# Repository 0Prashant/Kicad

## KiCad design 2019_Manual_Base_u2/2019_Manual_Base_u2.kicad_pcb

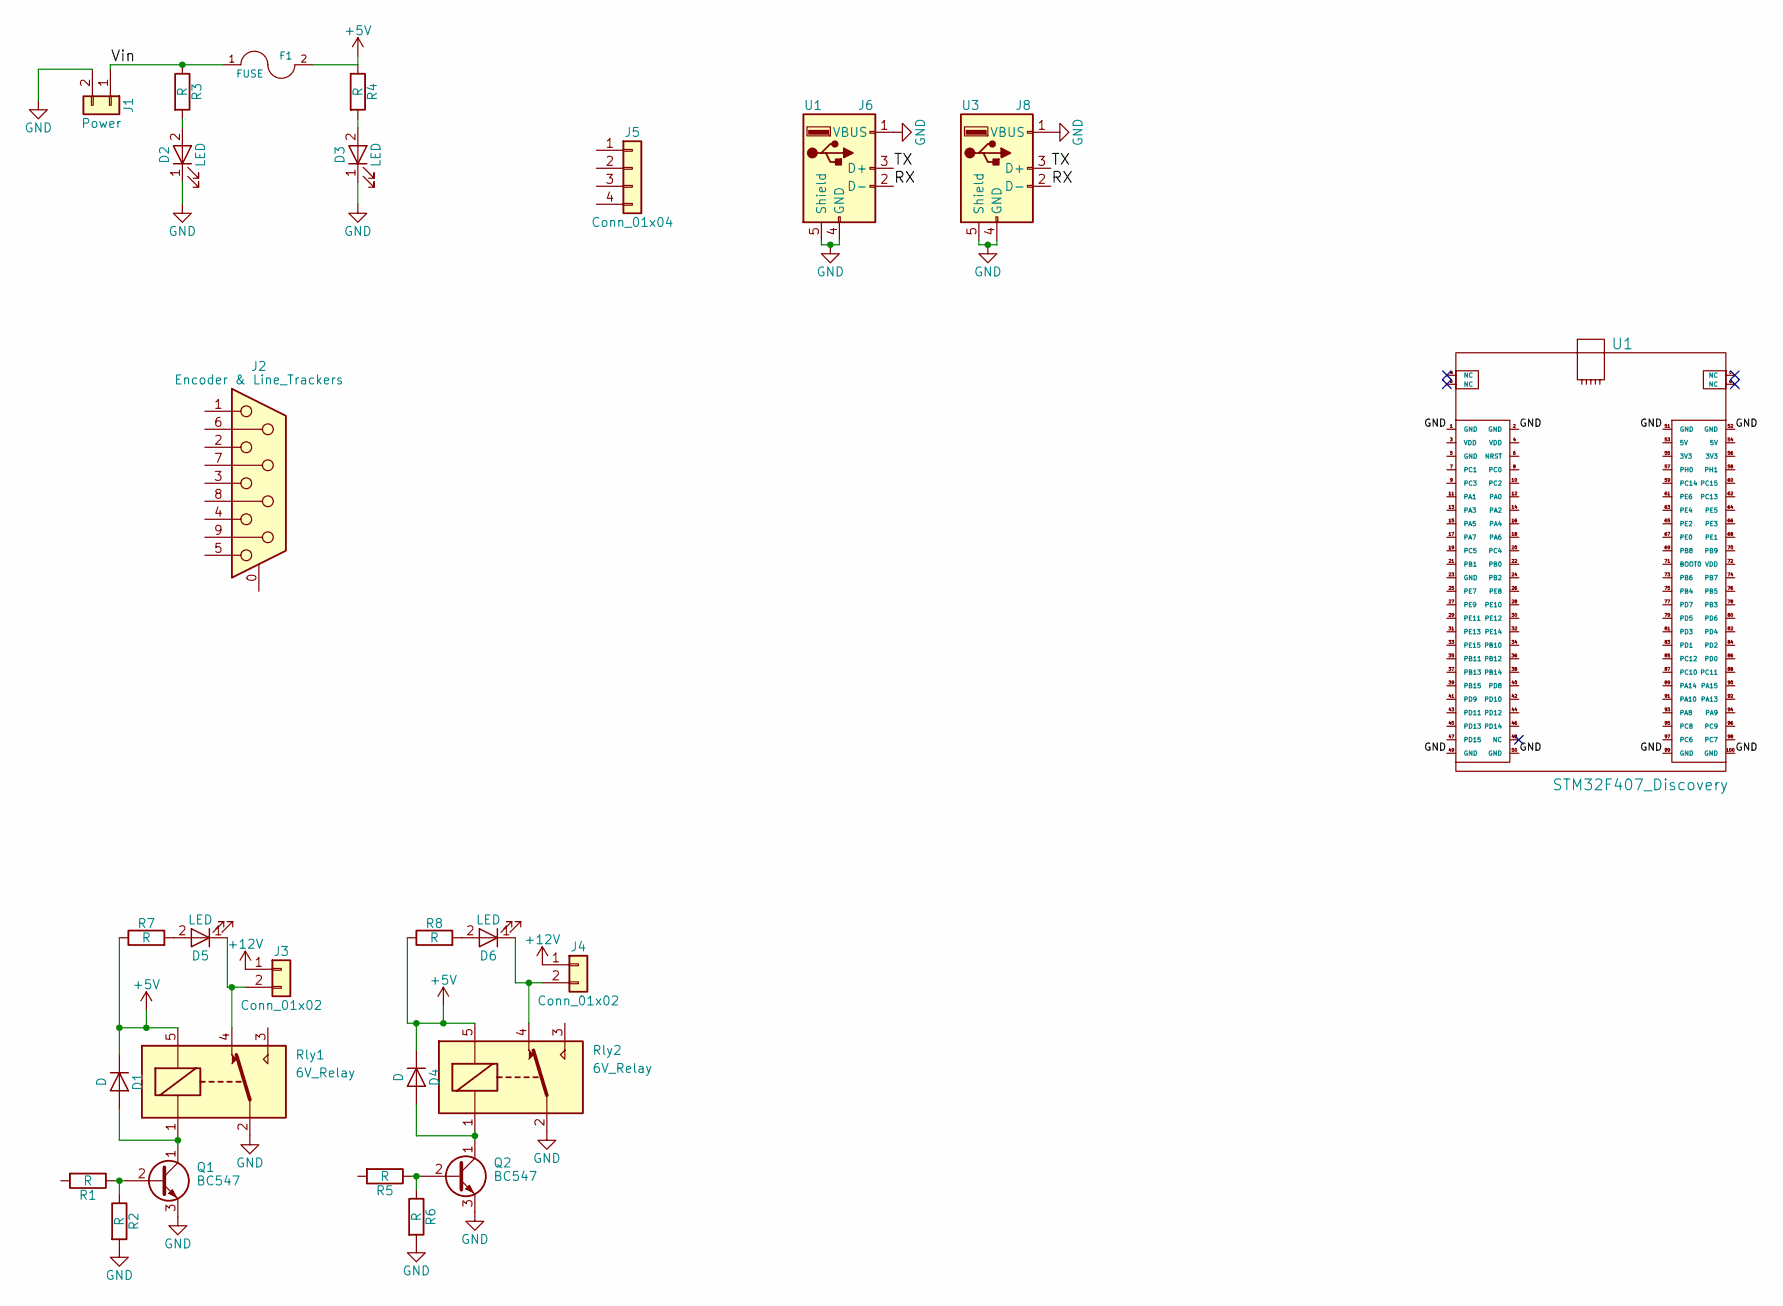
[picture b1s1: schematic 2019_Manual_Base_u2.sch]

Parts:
D1, D4: D; Diode_Small
D2, D3, D5, D6: LED; LED_D3.0mm
F1: FUSE; Fuse_Holder
J1: Power; Solar_Connector
J2: Encoder & Line_Trackers; Connector_DB_9
J3, J4: Conn_01x02; Connector_Bornier_2
J5: Conn_01x04; Pin_Header_Straight_1x04_Pitch2.54mm
J6: U1; Connector_USB
J8: U3; Connector_USB
Q1, Q2: BC547
R1, R2, R3, R4, R5, R6, R7, R8: R; Resistor_small
Rly1, Rly2: 6V_Relay; Relay_6V
U1: STM32F407_Discovery

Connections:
+5V: D1.1 (K), D4.1 (K), F1.2, R4.1, R7.1, R8.1, Rly1.5, Rly2.5
+12V: J3.1, J4.1
/RX: J6.2 (D-), J8.2 (D-)
/TX: J6.3 (D+), J8.3 (D+)
/Vin: F1.1, J1.1, R3.1
GND: D2.1 (K), D3.1 (K), J1.2, J6.1 (VBUS), J6.4 (GND), J6.5 (Shield), J8.1 (VBUS), J8.4 (GND), J8.5 (Shield), Q1.3 (E), Q2.3 (E), R2.2, R6.2, Rly1.2, Rly2.2, U1.1 (GND), U1.2 (GND), U1.49 (GND), U1.50 (GND), U1.51 (GND), U1.52 (GND), U1.99 (GND), U1.100 (GND)
unnamed: D1.2 (A), Q1.1 (C), Rly1.1
unnamed: D2.2 (A), R3.2
unnamed: D3.2 (A), R4.2
unnamed: D4.2 (A), Q2.1 (C), Rly2.1
unnamed: D5.1 (K), J3.2, Rly1.4
unnamed: D5.2 (A), R7.2
unnamed: D6.1 (K), J4.2, Rly2.4
unnamed: D6.2 (A), R8.2
unnamed: Q1.2 (B), R1.1, R2.1
unnamed: Q2.2 (B), R5.1, R6.1

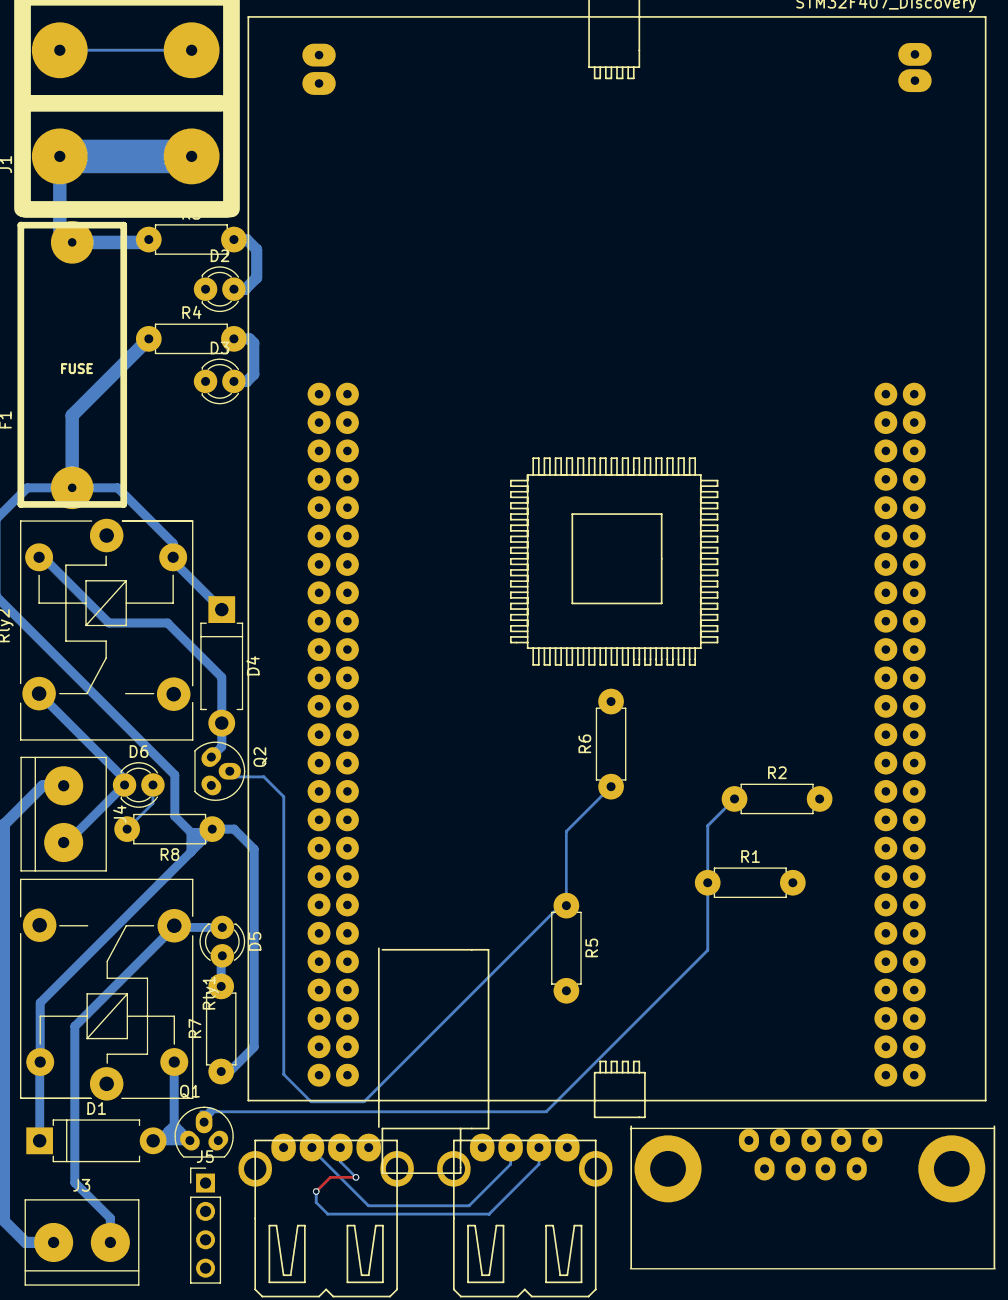
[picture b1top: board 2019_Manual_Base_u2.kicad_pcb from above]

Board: 2 copper layers, 27 parts (0 on the bottom side), 16 nets.

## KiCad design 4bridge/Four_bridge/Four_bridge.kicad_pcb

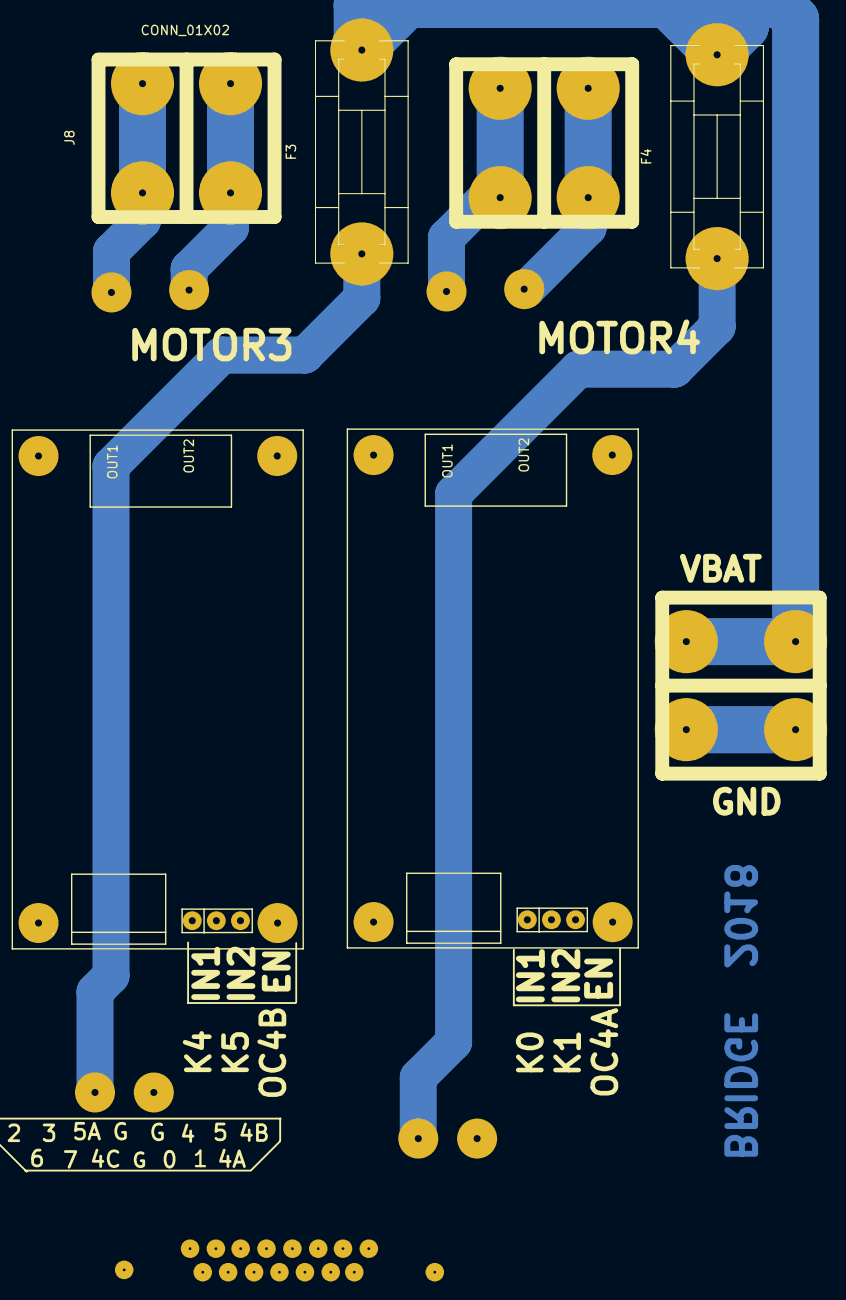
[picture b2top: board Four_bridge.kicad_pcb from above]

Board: 2 copper layers, 8 parts (0 on the bottom side), 14 nets.

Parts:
F3, F4: Fuse; Fuseholder5x20_horiz_SemiClosed_Casing10x25mm
J2: DB15_MALE; DB15MC
J4, J8, J11: CONN_01X02; Solar_connector
J7: H-Bridge3; H_Bridge
J10: H-Bridge4; H_Bridge

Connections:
/GND: J2.4, J2.5, J2.12, J4.2, J7.7, J10.7
/M31: J2.7, J7.4
/M32: J2.6, J7.5
/M41: J2.14, J10.4
/M42: J2.15, J10.5
/OUT31: J7.1, J8.1
/OUT32: J7.2, J8.2
/OUT41: J10.1, J11.1
/OUT42: J10.2, J11.2
/PWM3: J2.8, J7.3
/PWM4: J2.13, J10.3
/VBAT: F3.2, F4.2, J4.1
/VBAT3: F3.1, J7.6
/VBAT4: F4.1, J10.6

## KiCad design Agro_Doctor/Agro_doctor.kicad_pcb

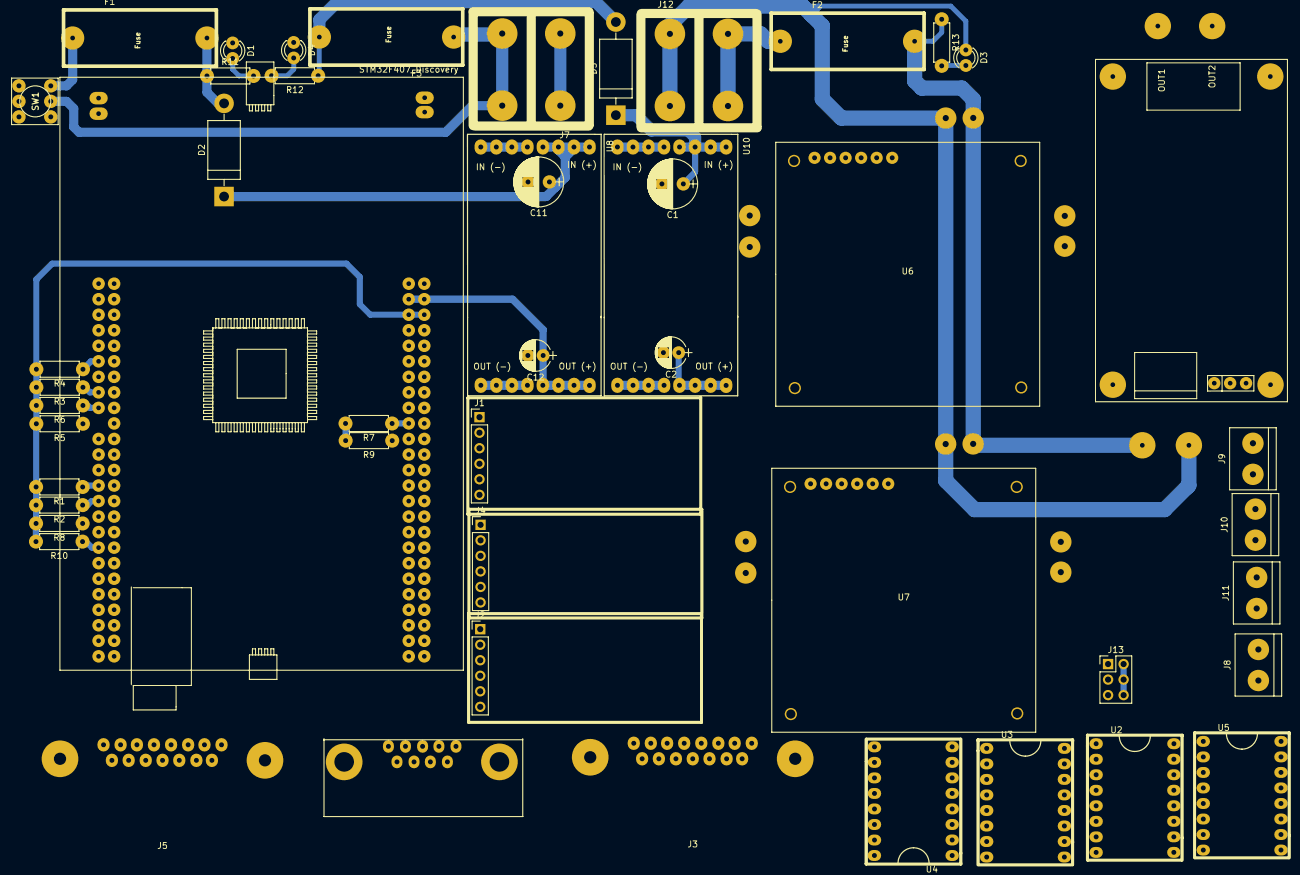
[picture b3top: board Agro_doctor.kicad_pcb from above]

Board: 2 copper layers, 49 parts (0 on the bottom side), 33 nets.

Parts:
C1, C11: 100uf; Capacitor_100uF
C2, C12: 10uf; Capacitor_10uF
D1, D3, D4: LED; LED_D3.0mm
D2, D5: D; Diode_Medium
F1, F2, F3: Fuse; Fuse_Holder
J1, J2, J4: Bluetooth; Pin_Header_Straight_1x06_Pitch2.54mm
J3: 3STEPPER,1SERVO; Connector_DB15
J5: Encoders, Stepper1; Connector_DB15
J6: 3 MPU, HUMIDITY, PH; Connector_DB_9
J7: Power_Logic; Solar_Connector
J8: M1; Connector_Bornier_2
J9: M4; Connector_Bornier_2
J10: M2; Connector_Bornier_2
J11: M3; Connector_Bornier_2
J12: Power_Motor; Solar_Connector
J13: MS_Conn; Pin_Header_Straight_2x03_Pitch2.54mm
R1, R2, R3, R4, R5, R6, R7, R8, R9, R10: 10K; Resistor_small
R11, R13: 1k5; Resistor_small
R12: R; Resistor_small
SW1: SW_DIP_x01; DIP_Switch
U1: Motor_Driver; H_Bridge
U2: A4988_1; A4998
U3: A4988_2; A4998
U4: A4988_3; A4998
U5: A4988_4; A4998
U6: L298_M2,3; L298
U7: L298_M4; L298
U8: Buck; Buck_Regulator
U9: STM32F407_Discovery
U10: Boost; Buck_Regulator

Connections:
+3V3: J6.5, R1.2, R2.2, R3.2, R4.2, R5.2, R6.2, R7.2, R8.2, R9.2, R10.2, U9.55, U9.56
+5V: C12.1, J1.5, J2.5, J3.8, J4.5, J5.14, J6.9, J13.4, J13.5, J13.6, U8.3, U9.53, U9.54
+12V: F3.2, J7.2, SW1.1
/12VMOT: F2.1, R13.1, U1.6, U6.1, U7.1
/18V: C2.1, U10.3
/E1_CHA: J5.13, R1.1, U9.27
/E1_CHB: J5.12, R2.1, U9.29
/E2_CHA: J5.11, R3.1, U9.15
/E2_CHB: J5.5, R4.1, U9.11
/E3_CHA: J5.4, R5.1, U9.18
/E3_CHB: J5.3, R6.1, U9.17
/GMOT: D3.1, J12.1, U1.7, U6.2, U7.2
/I2C1_SCL: J6.7, R7.1, U9.69
/I2C1_SDA: J6.6, R9.1, U9.70
/I2C2_SCL: J6.4, R8.1, U9.34
/I2C2_SDA: J6.1, R10.1, U9.35
/SERVO: J3.15, U9.91
/U1_RX: J1.3, U9.74
/U1_TX: J1.2, U9.73
/U2_RX: J2.3, U9.13
/U2_TX: J2.2, U9.14
/U3_RX: J4.3, U9.88
/U3_TX: J4.2, U9.87
GND: C1.2, C2.2, C11.2, C12.2, D1.1, D4.1, J1.4, J2.4, J3.7, J4.4, J5.7, J6.8, J7.1, U8.2, U8.4, U9.1, U9.2, U9.49, U9.50, U9.51, U9.52, U9.99, U9.100, U10.2, U10.4
unnamed: C1.1, D5.1, U10.1
unnamed: C11.1, D2.1, U8.1
unnamed: D1.2, R11.2
unnamed: D2.2, F1.1, R11.1
unnamed: D3.2, R13.2
unnamed: D4.2, R12.2
unnamed: D5.2, F3.1, R12.1
unnamed: F1.2, SW1.2
unnamed: F2.2, J12.2

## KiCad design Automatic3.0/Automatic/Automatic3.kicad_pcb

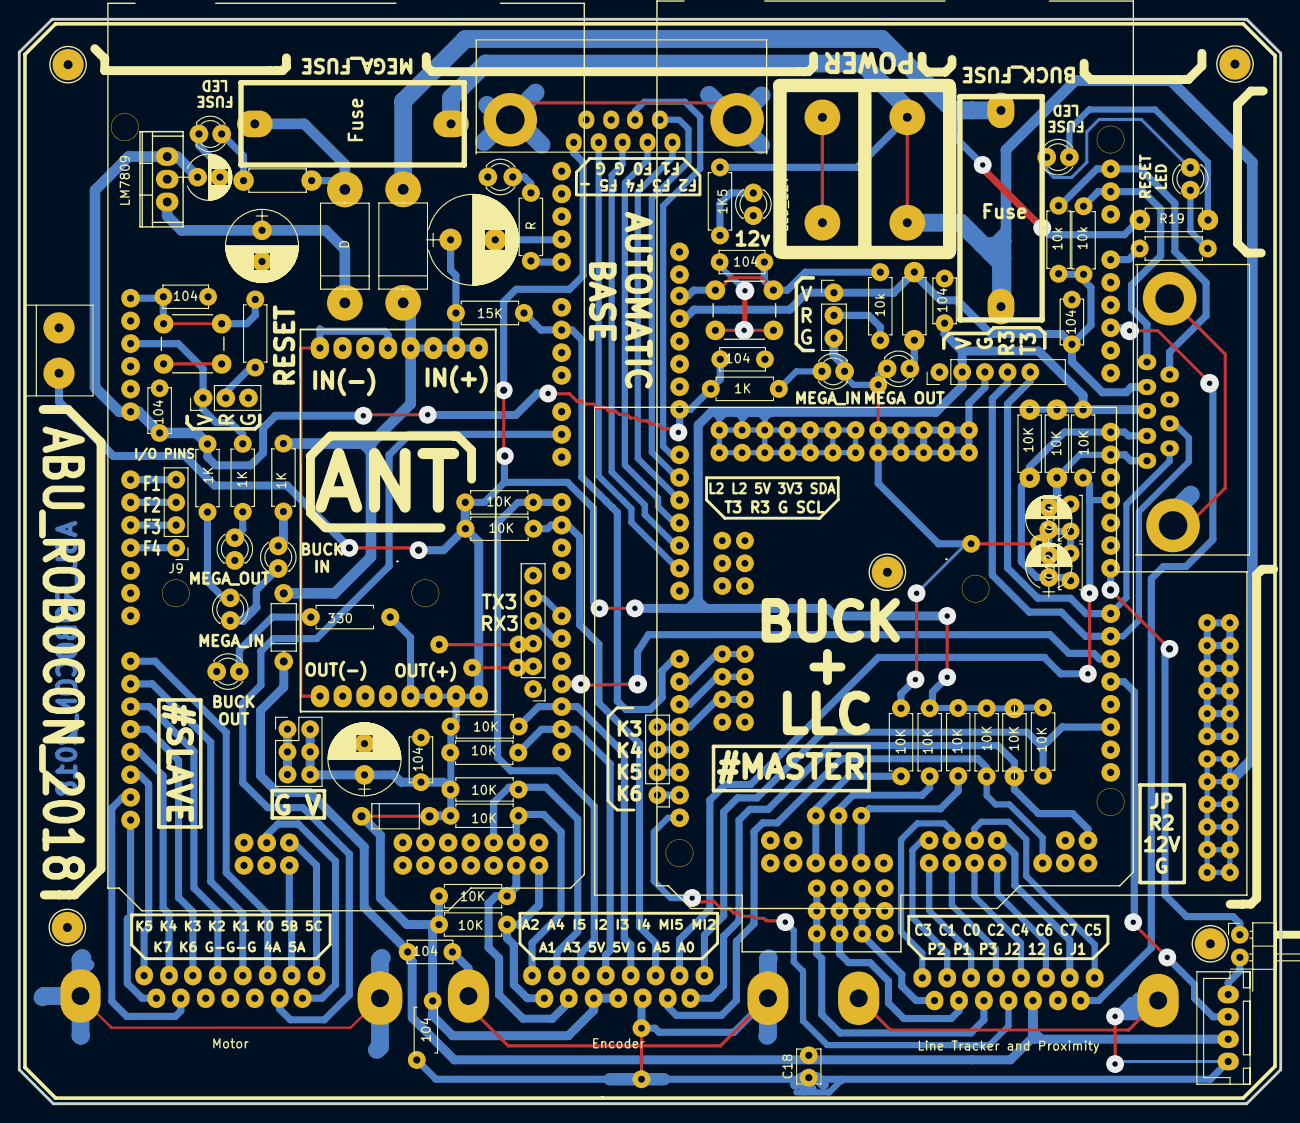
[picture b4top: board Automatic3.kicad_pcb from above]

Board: 2 copper layers, 141.2 x 121.4 mm, 101 parts (0 on the bottom side), 97 nets.

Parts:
C1, C2, C3, C5, C6, C7, C12, C14, C15, C16, C17: 104; Capacitor_Disc_Medium
C4: 1000uF; Capacitor_1000uF
C8, C11: 10uf; Capacitor_10uF
C9, C13: 100uF; Capacitor_100uF
C10: 10uF; Capacitor_10uF
C18: C; Capacitor_Disc_Small
D2, D3: D; Diode_small
D4, D12, D14, D17: LED; LED_D3.0mm
D5: LED_12V; LED_D3.0mm
D6, D7: MEGA_IN; LED_D3.0mm
D8: BUCK_OUT; LED_D3.0mm
D9: BUCK_IN; LED_D3.0mm
D10, D11: D; D_DO-27_P12.70mm_Horizontal
D13: MEGA_OUT; LED_D3.0mm
D19: MEGA OUT; LED_D3.0mm
F1, F2: Fuse; Fuse_Holder
J1: GND_VCC; Pin_Header_Straight_2x03_Pitch2.54mm
J2, J4, J5, J8, J24: CONN_01X01; 1_Pin
J3: Compass & throwing; Connector_DB_9
J6: Zone_Switches; Connector_DB_9
J7, J9: I/O PINS; Pin_Header_Straight_1x04_Pitch2.54mm
J10: Line Tracker and Proximity; Connector_DB15
J11, J14, J19, J21, J22: J; Jumper
J12, J20: Bluetooth; Pin_Header_Straight_1x06_Pitch2.54mm
J13: Encoder; Connector_DB15
J15: Motor; Connector_DB15
J16: CONN_01X02; Solar_Connector
J17, J18: Reset_Jumper; Pin_Header_Straight_1x03_Pitch2.54mm
J23: BUCK+LLC
J25: JST; JST_XH_B04B-XH-A_04x2.50mm_Straight
J26: FAN; Connector_Bornier_2
J27: J_PULSE; Pin_Header_Angled_1x02_Pitch2.54mm
R1: 15K; Resistor_small
R2, R4, R5, R6, R7, R8, R9, R10, R11, R12, R13, R25, R26, R32, R33, R34: 10K; Resistor_small
R3: 10K; R_Axial_DIN0207_L6.3mm_D2.5mm_P10.16mm_Horizontal
R14: 1K5; Resistor_small
R15, R16, R18, R20: 1K; Resistor_small
R17, R19, R35, R42: 330; Resistor_small
R21, R22, R23, R24: 10k; Resistor_small
R28, R31: R; Resistor_small
SW1, SW2: Reset; Push_Button
U1, U2: Arduino_Mega2560_Shield
U4: LM7809; Voltage_Regulators
U5: Buck; Buck_Regulator

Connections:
+5V: C2.1, C13.1, C16.1, C17.1, D2.1, D2.2, J1.2, J1.4, J1.6, J3.3, J6.1, J12.2, J13.12, J13.13, J20.2, J21.1, J23.3, J26.2, R2.2, R3.1, R4.2, R5.1, R6.2, R7.1, R8.2, R9.1, R10.2, R11.1, R12.2, R13.1, R17.2, R25.1, R26.1, R33.1, R34.1, U5.3
+9V: C1.2, C10.1, C15.2, R15.2, R16.2, U1.VIN, U2.VIN, U4.3
+12V: F1.2, F2.2, J16.1, J23.2, R14.2
/3V3: C6.1, J3.2, J17.1, R23.1, R24.1, R35.2, U1.3V3
/5VV: J18.1, R20.2, U2.5V1
/12VV: C4.1, D3.2, D11.1, R1.1, R18.2, U5.1
/12VVD: C5.2, C18.2, D3.1, J10.11, J25.3
/INT: R1.2, U1.A8, U2.10
/INT2: J13.1, R2.1, U1.19
/INT5: J13.2, R12.1, U1.3
/JP1: J10.9, U1.10
/JP2: J10.12, U1.A15
/JP3: J25.1, J27.2
/L1: C8.1, C12.1, J3.4, R25.2, U1.6
/L2: C11.2, C14.2, J3.5, R26.2, U1.5
/LED1: J23.10, U1.A9
/LED2: J23.11, U1.A10
/LED3: J7.4, J23.12, U1.A11
/OC4A: J15.10, U2.6
/OC5A: J15.9, U2.46
/OC5B: J15.2, U2.45
/OC5C: J15.1, U2.44
/PA0: J13.9, R3.2, U1.22
/PA1: J13.15, R5.2, U2.23
/PA2: J13.8, R7.2, U2.24
/PA3: J13.14, R9.2, U2.25
/PA4: J13.7, R11.2, U2.26
/PA5: J13.10, R13.2, U1.27
/PC0: J10.6, U1.37
/PC1: J10.7, U1.36
/PC2: J10.5, U1.35
/PC3: J10.8, U1.34
/PC4: J10.4, U1.33
/PC5: J10.1, U1.32
/PC6: J10.3, U1.31
/PC7: J10.2, U1.30
/PF0: J6.8, U1.A0
/PF1: J6.9, U1.A1
/PF2: J6.5, U1.A2
/PF3: J6.4, U1.A3
/PF4: J6.3, U1.A4
/PF5: J6.2, U1.A5
/PK0: J15.3, U2.A8
/PK1: J15.4, U2.A9
/PK2: J15.5, U2.A10
/PK3: J15.6, U2.A11
/PK4: J15.7, U2.A12
/PK5: J15.8, U2.A13
/PK6: J15.14, U2.A14
/PK7: J15.15, U2.A15
/PR1: J10.14, J23.4
/PR1o: J23.7, R34.2, U1.45
/PR2: J10.15, J23.5
/PR2o: J23.8, R33.2, U1.43
/PR3: J10.13, J23.6
/PR3o: J23.9, R32.2, U1.47
/RESET1: C7.2, R21.2, SW1.2, U1.RST1
/RESET2: C3.2, R22.2, SW2.2, U2.RST1
/RX0: J27.1, U1.0
/RX2: J25.2, U1.17
/RX3: J3.8, J12.4, U1.15
/SCL: J3.6, R23.2, U1.SCL
/SDA: J3.1, R24.2, U1.SDA
/SINT2: J13.5, R6.1, U2.19
/SINT3: J13.4, R8.1, U2.18
/SINT4: J13.3, R10.1, U2.2
/SINT5: J13.6, R4.1, U2.3
/SRX3: J20.4, U2.15
/STX3: J20.5, U2.14
/TX2: U1.16, U2.17
/TX3: J3.9, J12.5, U1.14
GND: C1.1, C2.2, C3.1, C4.2, C5.1, C6.2, C7.1, C8.2, C9.2, C10.2, C11.1, C12.2, C13.2, C14.1, C15.1, C16.2, C17.2, C18.1, D4.1, D5.1, D6.1, D7.1, D8.1, D9.1, D12.1, D13.1, D14.1, D17.1, D19.1, J1.1, J1.3, J1.5, J3.0, J3.7, J6.0, J6.6, J10.0, J10.10, J11.1, J12.3, J13.0, J13.11, J14.1, J15.0, J15.11, J15.12, J15.13, J16.2, J17.3, J18.3, J19.1, J20.3, J22.1, J23.1, J25.4, J26.1, R32.1, SW1.1, SW2.1, U1.GND1, U1.GND2, U2.GND1, U2.GND2, U2.GND5, U4.2, U5.2, U5.4
unnamed: C9.1, D10.1, U4.1
unnamed: D4.2, R31.1
unnamed: D5.2, R14.1
unnamed: D6.2, R15.1
unnamed: D7.2, R16.1
unnamed: D8.2, R17.1
unnamed: D9.2, R18.1
unnamed: D10.2, F1.1, R42.2
unnamed: D11.2, F2.1, R19.2
unnamed: D12.2, R19.1
unnamed: D13.2, R20.1
unnamed: D14.2, R28.1
unnamed: D17.2, R42.1
unnamed: D19.2, R35.1
unnamed: J7.1, U1.A14
unnamed: J7.2, U1.A13
unnamed: J7.3, U1.A12
unnamed: J9.1, U2.A4
unnamed: J9.2, U2.A3
unnamed: J9.3, U2.A2
unnamed: J9.4, U2.A1
unnamed: J17.2, R21.1
unnamed: J18.2, R22.1
unnamed: R28.2, U1.13
unnamed: R31.2, U2.13

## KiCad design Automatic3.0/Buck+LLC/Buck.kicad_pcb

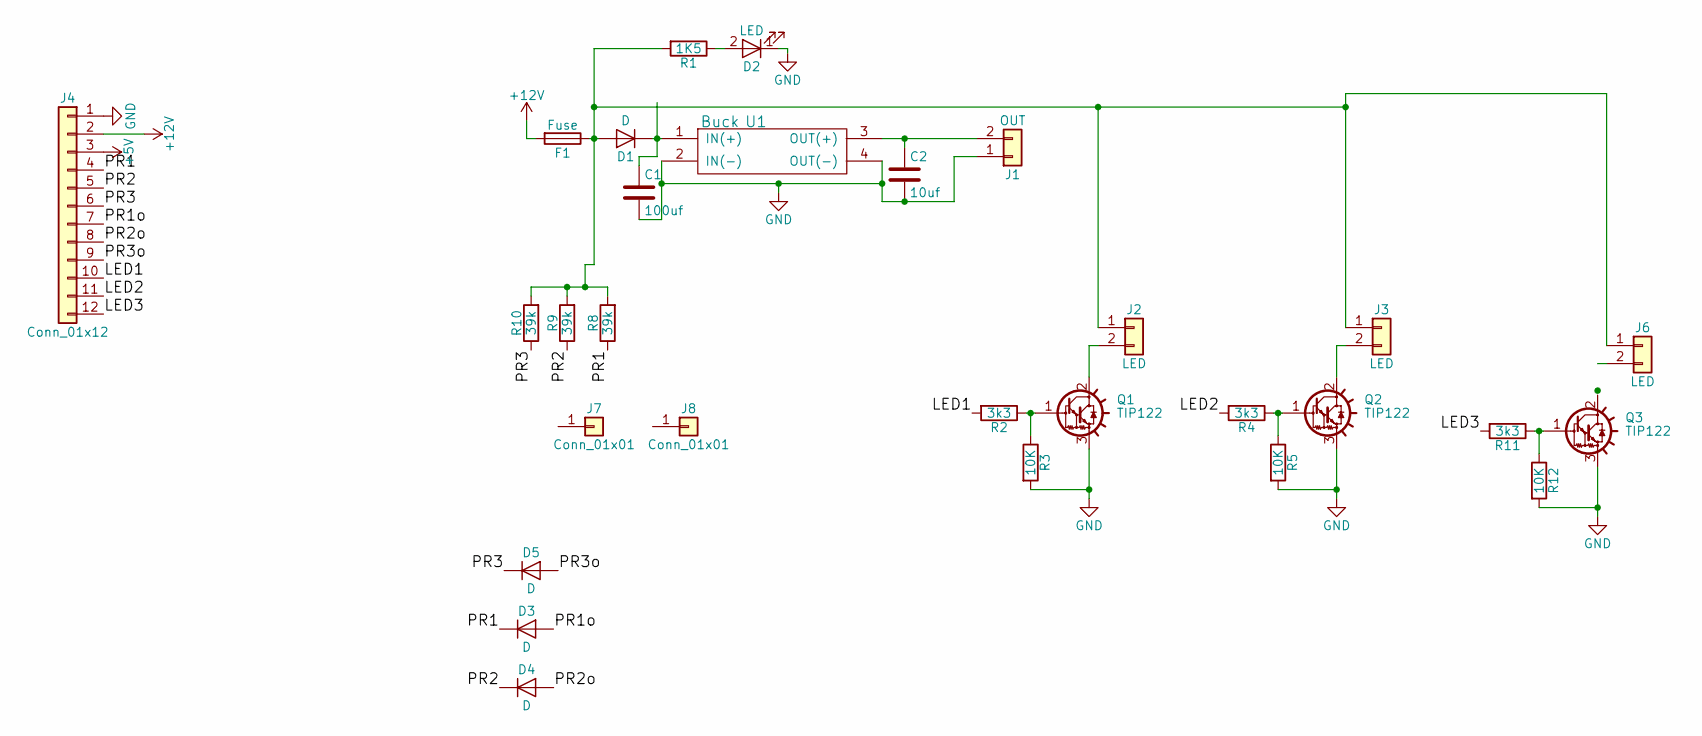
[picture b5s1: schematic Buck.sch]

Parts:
C1: 100uf; Capacitor_100uF
C2: 10uf; Capacitor_10uF
D1: D; Diode_Medium
D2: LED; LED_D3.0mm
D3, D4, D5: D; Diode_small
F1: Fuse; Fuse_Holder
J1: OUT; Connector_Bornier_2
J2, J3, J6: LED; Connector_Bornier_2
J4: Conn_01x12; BUCK+LLC
J7, J8: Conn_01x01; 1_Pin
Q1, Q2, Q3: TIP122; Voltage_Regulators
R1: 1K5; Resistor_small
R2, R4, R11: 3k3; Resistor_small
R3, R5, R12: 10K; Resistor_small
R8, R9, R10: 39k; Resistor_small
U1: Buck; Buck_Regulator

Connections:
+5V: J4.3
+12V: F1.2, J4.2
/LED1: J4.10, R2.2
/LED2: J4.11, R4.2
/LED3: J4.12, R11.2
/PR1: D3.1 (K), J4.4, R8.1
/PR1o: D3.2 (A), J4.7
/PR2: D4.1 (K), J4.5, R9.1
/PR2o: D4.2 (A), J4.8
/PR3: D5.1 (K), J4.6, R10.1
/PR3o: D5.2 (A), J4.9
GND: C1.2, C2.2, D2.1 (K), J1.1, J4.1, Q1.3 (E), Q2.3 (E), Q3.3 (E), R3.2, R5.2, R12.2, U1.2 (IN(-)), U1.4 (OUT(-))
unnamed: C1.1, D1.1 (K), U1.1 (IN(+))
unnamed: C2.1, J1.2, U1.3 (OUT(+))
unnamed: D1.2 (A), F1.1, J2.1, J3.1, J6.1, R1.2, R8.2, R9.2, R10.2
unnamed: D2.2 (A), R1.1
unnamed: J2.2, Q1.2 (C)
unnamed: J3.2, Q2.2 (C)
unnamed: Q1.1 (B), R2.1, R3.1
unnamed: Q2.1 (B), R4.1, R5.1
unnamed: Q3.1 (B), R11.1, R12.1

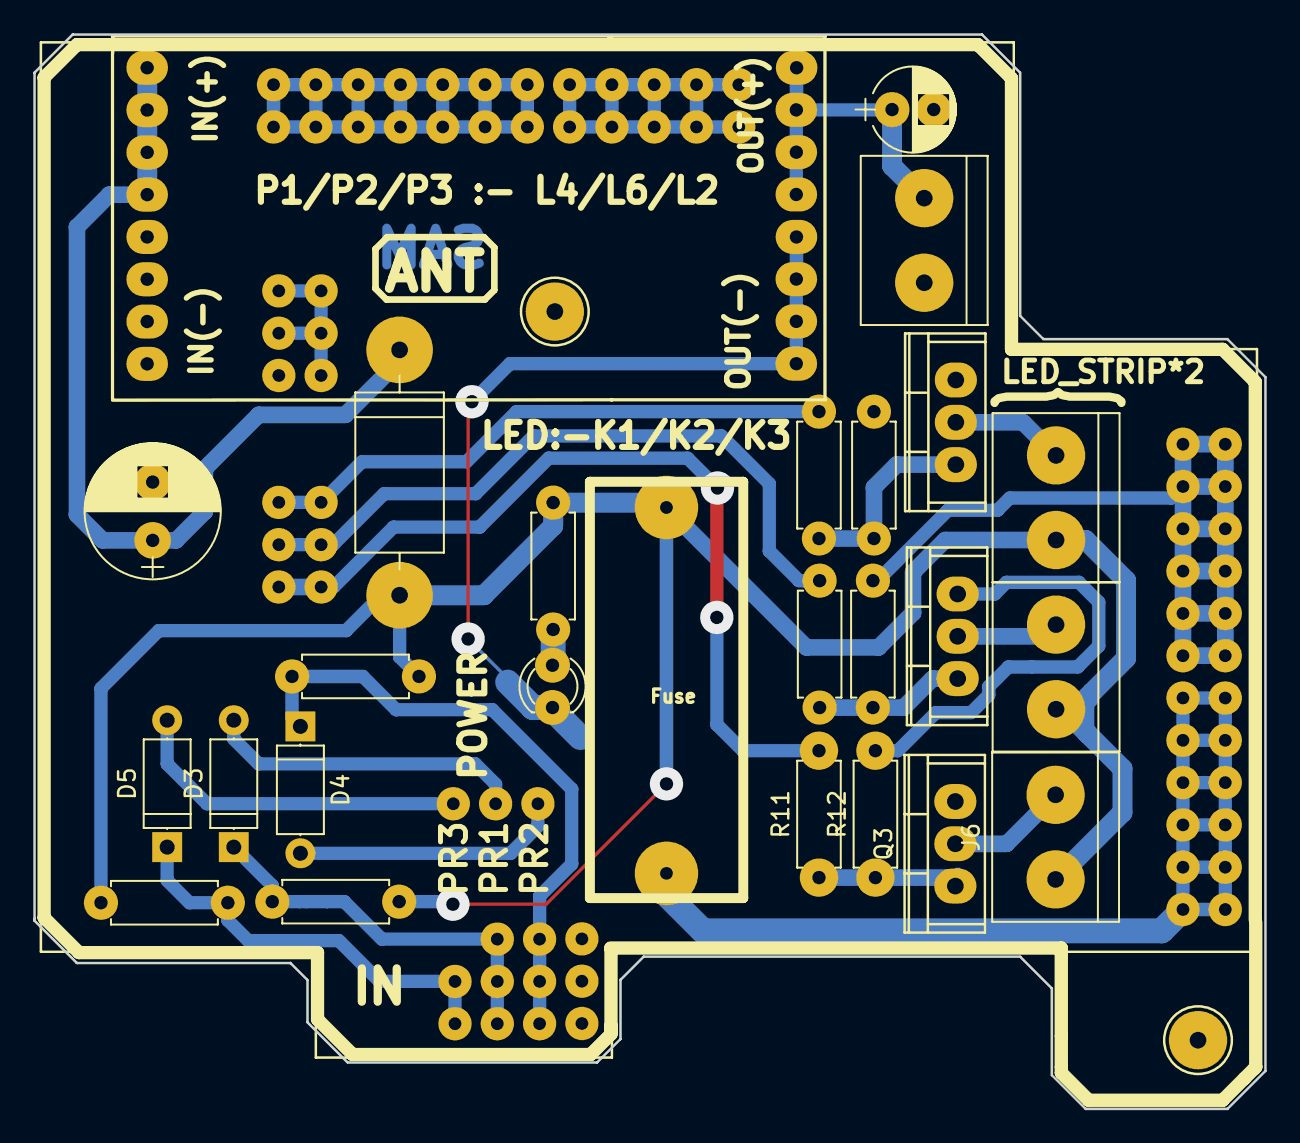
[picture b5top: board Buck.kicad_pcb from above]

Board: 2 copper layers, 73.9 x 64.5 mm, 29 parts (0 on the bottom side), 20 nets.

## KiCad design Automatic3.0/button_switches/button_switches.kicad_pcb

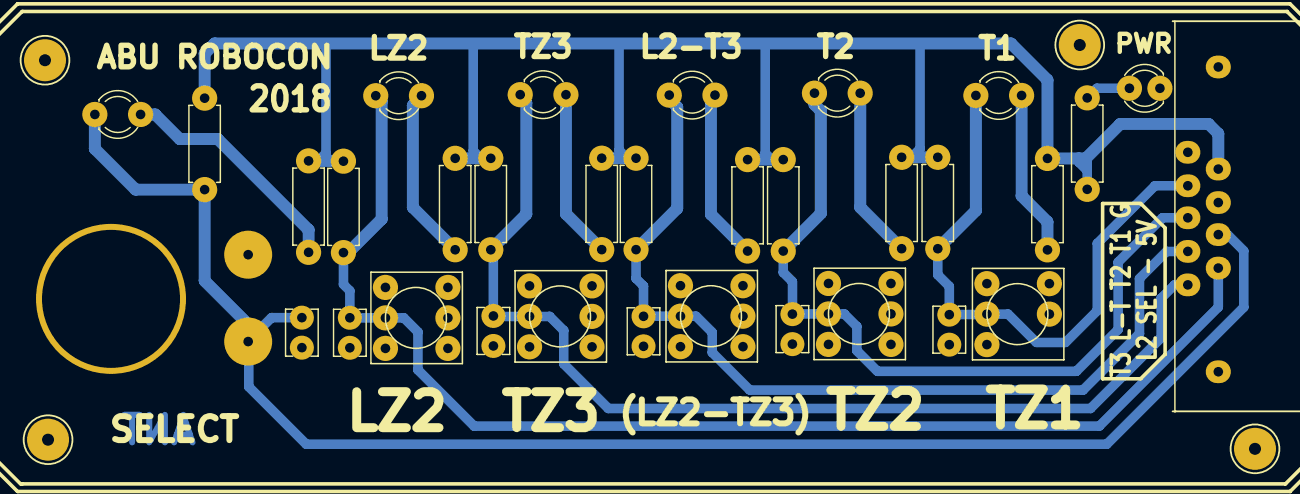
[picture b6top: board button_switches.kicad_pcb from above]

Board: 2 copper layers, 37 parts (0 on the bottom side), 15 nets.

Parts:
C1, C2, C3, C4, C5, C6: 104; Capacitor_Disc_Small
D1: PWR; LED_D3.0mm
D2, D3, D4, D5, D6, D7: LED; LED_D3.0mm
J1: DB9_Female_MountingHoles; Connector_DB_9
J2, J3, J4, J5: Conn_01x01; 1_Pin
R1, R2, R3, R4, R5, R6, R7: 330; Resistor_small
R9, R10, R11, R12, R13, R14: 10k; Resistor_small
SW1, SW2, SW3, SW4, SW5, SW6: SW_DPST; DIP_Switch

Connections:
+5V: J1.6, R1.2, R2.2, R3.2, R4.2, R5.2, R6.2, R7.2, R9.2, R10.2, R11.2, R12.2, R13.2, R14.2
/IN1: C1.1, D2.1, J1.5, R9.1, SW1.1
/IN2: C2.1, D3.1, J1.9, R10.1, SW2.1
/IN3: C3.1, D4.1, J1.8, R11.1, SW3.1
/IN4: C4.1, D5.1, J1.4, R12.1, SW4.1
/IN5: C5.1, D6.1, J1.3, R13.1, SW5.1
/IN6: C6.1, D7.1, J1.2, R14.1, SW6.1
GND: C1.2, C2.2, C3.2, C4.2, C5.2, C6.2, D1.1, J1.0, J1.1, SW1.2, SW1.3, SW1.4, SW2.2, SW2.3, SW2.4, SW3.2, SW4.2, SW4.3, SW4.4, SW5.2, SW5.3, SW5.4, SW6.2, SW6.3, SW6.4
unnamed: D1.2, R1.1
unnamed: D2.2, R2.1
unnamed: D3.2, R3.1
unnamed: D4.2, R4.1
unnamed: D5.2, R5.1
unnamed: D6.2, R6.1
unnamed: D7.2, R7.1
